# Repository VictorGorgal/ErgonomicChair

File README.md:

# ErgonomicChair
### Early stages of the project

This project consists of a "Smart Chair" with 8 sensors to monitor the user's posture.  
The chair connects to the desktop app via MQTT mainly, but can be connected via USB for troubleshooting.  
After the MQTT communication, the local server stores the data on the database using SQLite3.  
The UI was made using QT Designer and PyQt6:  

https://user-images.githubusercontent.com/94933775/169306776-e51699f6-c446-45f5-a91f-25bca25581f8.mp4

# TODO
- Refine the UI
- Integrate the UI with the database using the Interface class from the local server
- Display visualy the data on the app
- Add a way to communicate with the chair via USB for configuration purposes

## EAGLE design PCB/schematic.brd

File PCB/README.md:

# PCB
Schematics for the custom PCB developed for reading 9 force sensors (www.eletrogate.com/sensor-extensometro-transdutor-strain-gauge-bx120-3aa)

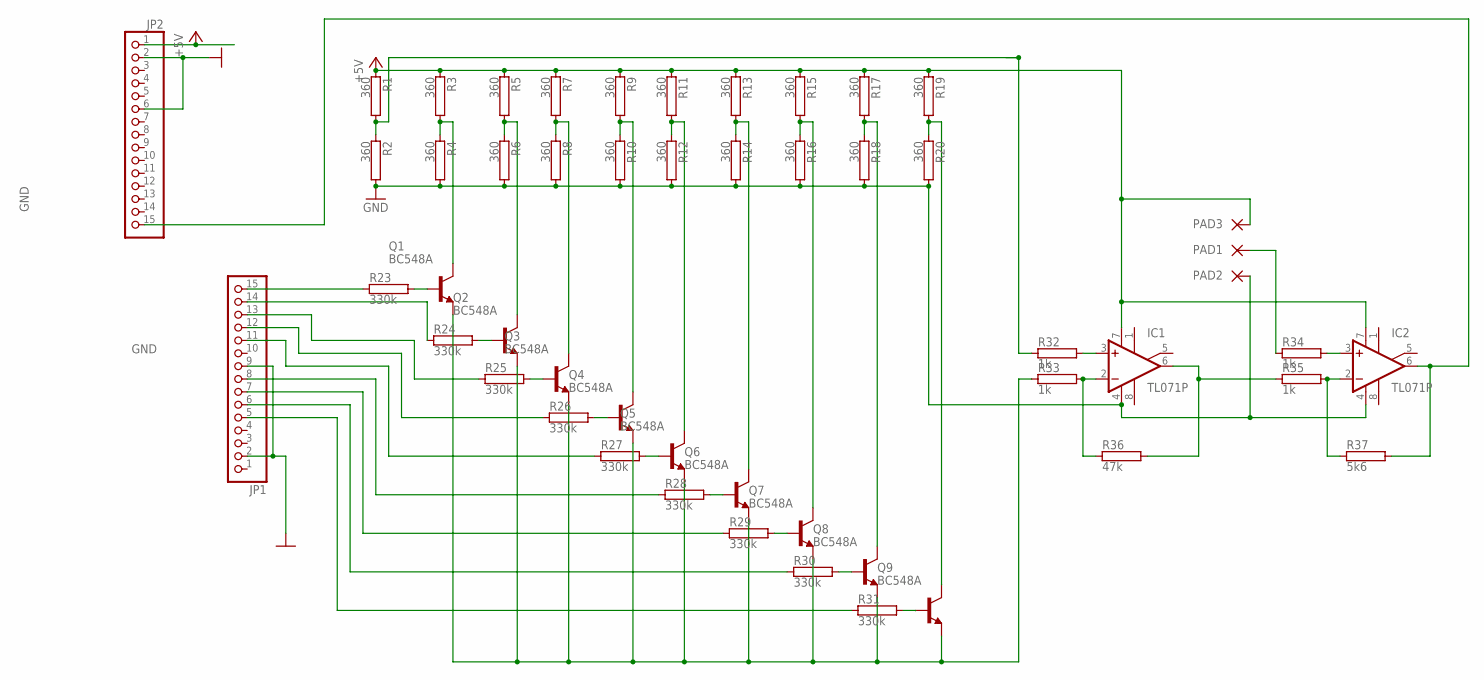
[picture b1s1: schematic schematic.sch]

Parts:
IC1, IC2: TL071P; DIL08
JP1, JP2: PINHD-1X15; 1X15
PAD1, PAD2, PAD3: WIREPADSMD5-1,8; 5-1,8
Q1, Q2, Q3, Q4, Q5, Q6, Q7, Q8, Q9: BC548A; TO92-EBC
R1, R2, R3, R4, R5, R6, R7, R8, R9, R10, R11, R12, R13, R14, R15, R16, R17, R18, R19, R20: 360; RS1/4
R23, R24, R25, R26, R27, R28, R29, R30, R31: 330k; RS1/4
R32, R33, R34, R35: 1k; RS1/4
R36: 47k; RS1/4
R37: 5k6; RS1/4

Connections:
+5V: IC1.7 (V+), IC2.7 (V+), JP2.1, PAD3.1, R1.1, R3.1, R5.1, R7.1, R9.1, R11.1, R13.1, R15.1, R17.1, R19.1
GND: IC1.4 (V-), IC2.4 (V-), JP1.2, JP1.9, JP2.2, JP2.6, PAD2.1, R2.2, R4.2, R6.2, R8.2, R10.2, R12.2, R14.2, R16.2, R18.2, R20.2
unnamed: R1.2, R2.1, R32.1
unnamed: Q1.C, R3.2, R4.1
unnamed: Q2.C, R5.2, R6.1
unnamed: Q3.C, R7.2, R8.1
unnamed: Q4.C, R9.2, R10.1
unnamed: Q5.C, R11.2, R12.1
unnamed: Q6.C, R13.2, R14.1
unnamed: Q7.C, R15.2, R16.1
unnamed: Q8.C, R17.2, R18.1
unnamed: Q9.C, R19.2, R20.1
unnamed: Q1.B, R23.2
unnamed: JP1.15, R23.1
unnamed: JP1.8, R28.1
unnamed: Q2.B, R24.2
unnamed: JP1.11, R27.1
unnamed: JP1.12, R26.1
unnamed: Q3.B, R25.2
unnamed: JP1.14, R24.1
unnamed: JP1.13, R25.1
unnamed: Q4.B, R26.2
unnamed: Q1.E, Q2.E, Q3.E, Q4.E, Q5.E, Q6.E, Q7.E, Q8.E, Q9.E, R33.1
unnamed: IC1.6 (OUT), R35.1, R36.2
unnamed: Q5.B, R27.2
unnamed: IC1.3 (+IN), R32.2
unnamed: IC2.3 (+IN), R34.2
unnamed: Q6.B, R28.2
unnamed: IC2.6 (OUT), JP2.15, R37.2
unnamed: IC2.2 (-IN), R35.2, R37.1
unnamed: Q7.B, R29.2
unnamed: JP1.7, R29.1
unnamed: PAD1.1, R34.1
unnamed: Q8.B, R30.2
unnamed: JP1.6, R30.1
unnamed: IC1.2 (-IN), R33.2, R36.1
unnamed: Q9.B, R31.2
unnamed: JP1.5, R31.1

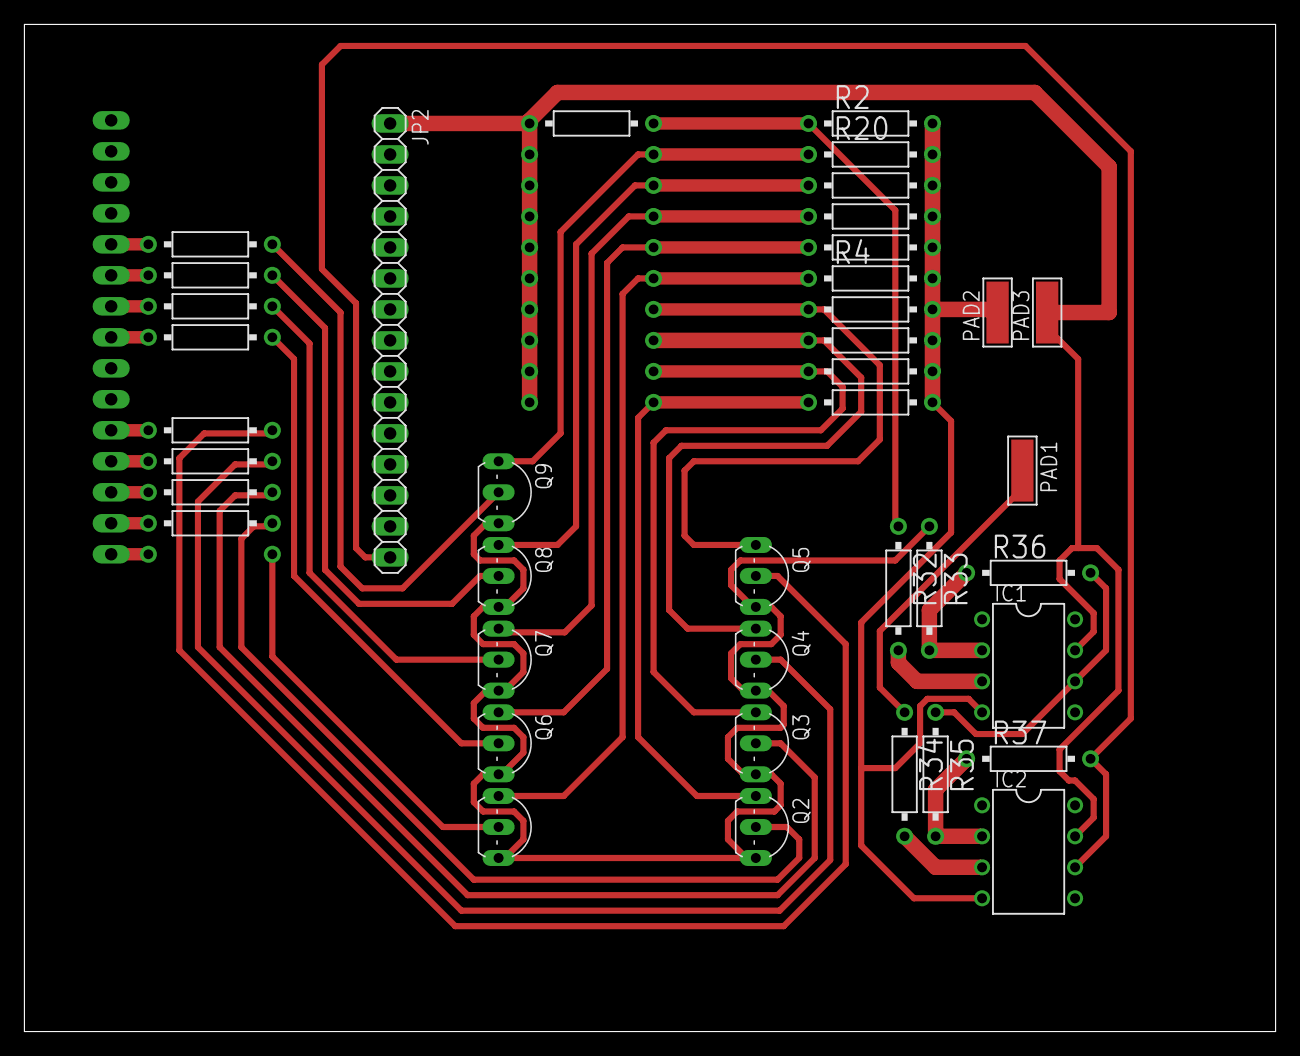
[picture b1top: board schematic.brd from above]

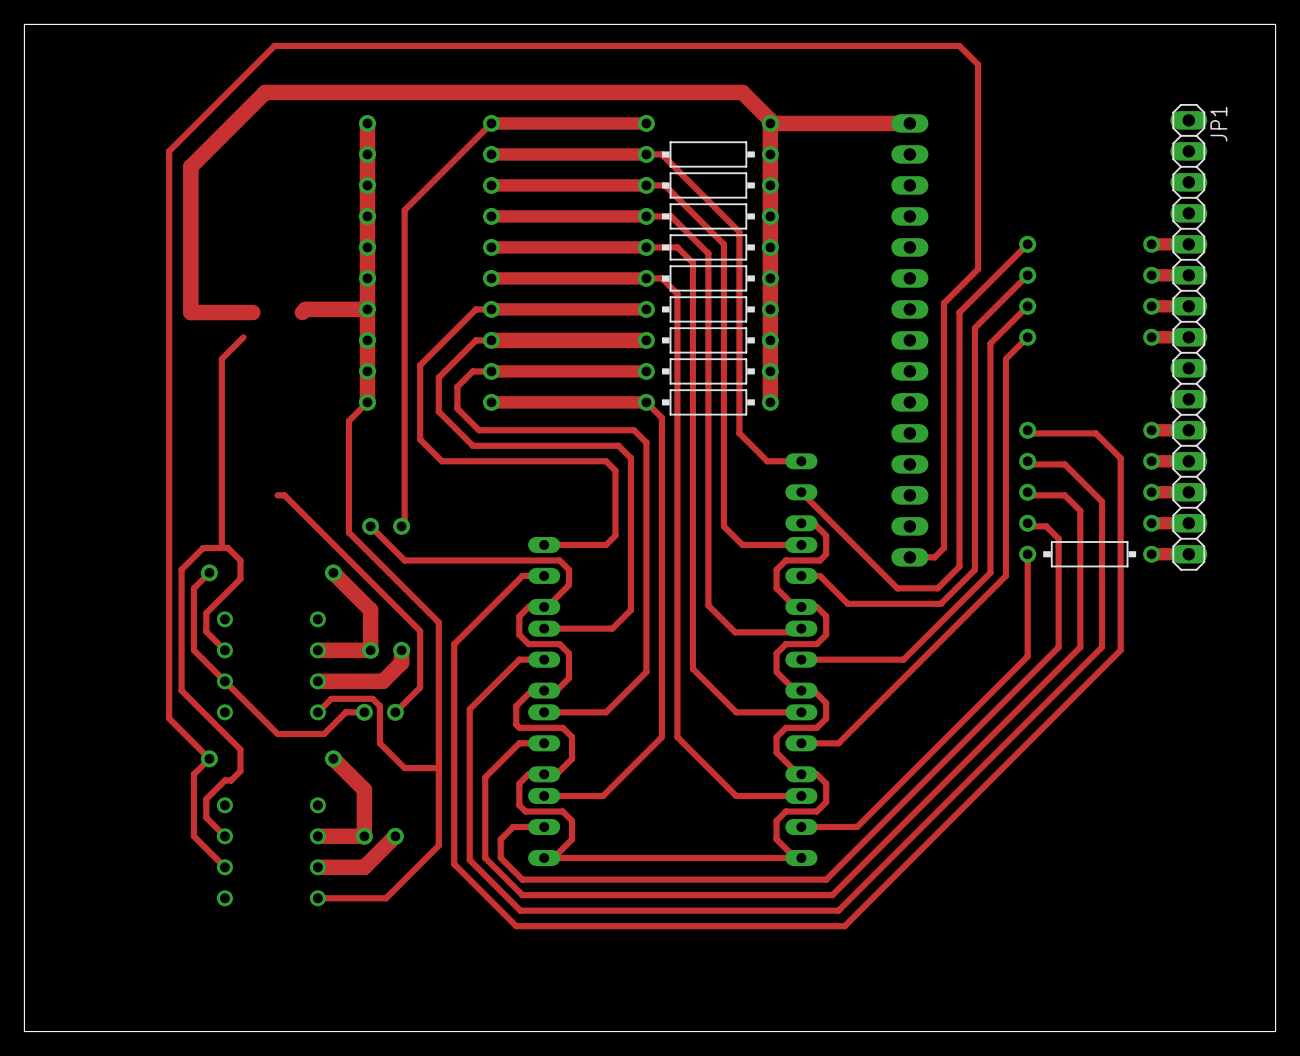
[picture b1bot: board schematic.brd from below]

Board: 2 copper layers, 102.5 x 82.5 mm, 51 parts (11 on the bottom side), 38 nets.

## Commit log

2022-05-17 Rename front_end/UI_base.py to UI/UI_base.py
2022-05-18 fixed label alignment error
2022-05-18 fixed lable alignment error
2022-05-18 test
2022-05-18 optmized highlight_button
2022-05-19 minor stuff
2022-05-19 added notification functionality
2022-05-19 added graph functionality
2022-05-19 changed notification library
2022-05-19 minor color pallet ajustments
2022-05-19 optmized graph rendering
2022-08-21 feat: Update project
2022-08-21 Update gitignore
2022-08-22 feat: Update gitignore
2022-08-22 feat: Add data to database
2022-08-22 feat: Update nodeMCU code
2022-08-22 feat: Update UI
2022-08-22 feat: Add daily data visualization
2022-08-22 feat: Update UI graph
2022-08-22 docs: Test
2022-09-20 feat: stuff
2022-09-21 feat: moah stuphh
2022-09-21 feat: moooooooooooooooooooooooooooooooooooooh
